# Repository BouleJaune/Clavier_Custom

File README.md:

# Clavier_Custom

Création d'un clavier avec un layout custom à partir de zéro.

Keyboard-layout.png et Raw_Layout_Data.txt représente le layout qui sera utilisé, généré via KLE.

CAD Case contient les fichiers .DXF pour découper les plaques d'aluminium qui serviront de "boitier".

CAD PCB contient le PCB exporté en .DXF pour comparer le placement des pas de vis avec le PCB.

PCB_vs_plaque.blender est le fichier blender permettant de voir qu'il n'y aura pas de soucis vis à vis des vis entrant en contact avec le PCB.

Scripting_Kicad contient les coordonnées des diodes et switchs sur le PCB ainsi qu'un petit script .py pour les placer automatiquement dans Kicad.

Kicad contient les librairies utilisées ainsi que le projet Kicad (PCB et& schématique).

Encore une hésitation sur l'utilisation d'une simple Teensy++ 2.0 ou alors la création complète du micro-contrôleur ce qui implique de burn un bootloader et gérer les soudures complexes.

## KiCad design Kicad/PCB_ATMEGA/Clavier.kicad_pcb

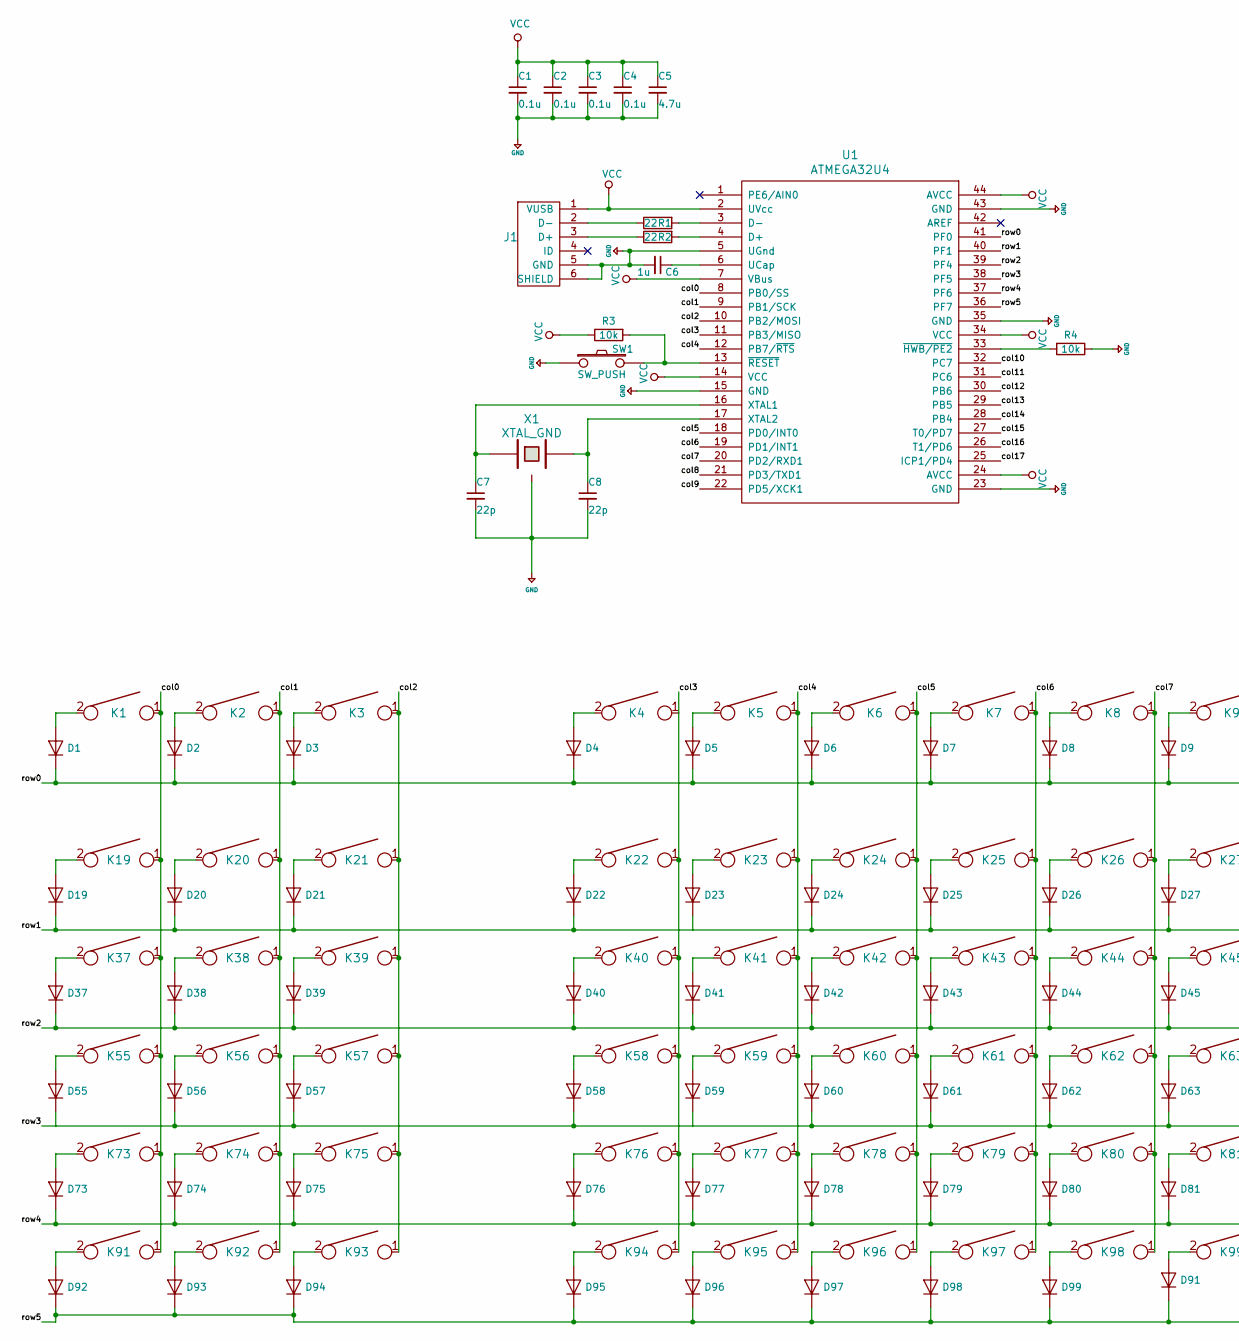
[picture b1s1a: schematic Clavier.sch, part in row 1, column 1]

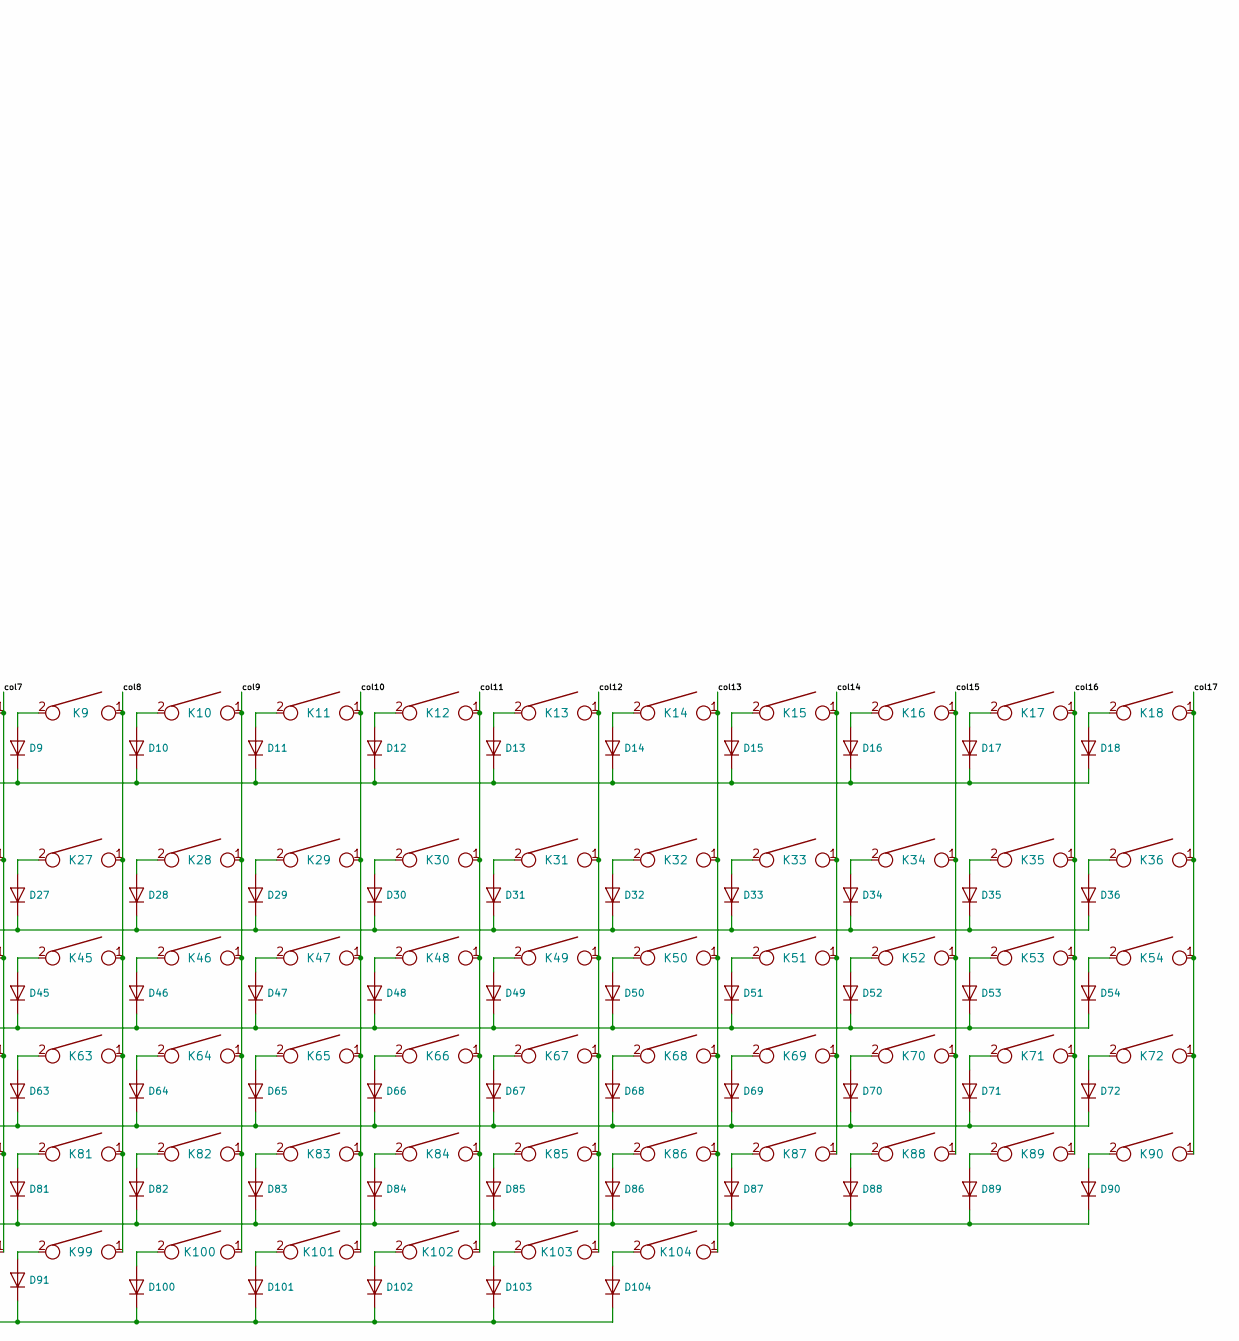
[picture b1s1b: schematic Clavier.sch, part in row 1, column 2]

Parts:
C1, C2, C3, C4: 0.1u; C_0805_2012Metric_Pad1.15x1.40mm_HandSolder
C5: 4.7u; C_0805_2012Metric_Pad1.15x1.40mm_HandSolder
C6: 1u; C_0805_2012Metric_Pad1.15x1.40mm_HandSolder
C7, C8: 22p; C_0805_2012Metric_Pad1.15x1.40mm_HandSolder
D1, D2, D3, D4, D5, D6, D7, D8, D9, D10, D11, D12, D13, D14, D15, D16, D17, D18, D19, D20, D21, D22, D23, D24, D25, D26, D27, D28, D29, D30, D31, D32, D33, D34, D35, D36, D37, D38, D39, D40, D41, D42, D43, D44, D45, D46, D47, D48, D49, D50, D51, D52, D53, D54, D55, D56, D57, D58, D59, D60, D61, D62, D63, D64, D65, D66, D67, D68, D69, D70, D71, D72, D73, D74, D75, D76, D77, D78, D79, D80, D81, D82, D83, D84, D85, D86, D87, D88, D89, D90, D91, D92, D93, D94, D95, D96, D97, D98, D99, D100, D101, D102, D103, D104: D; D_SOD123_axial
J1: USB_mini_micro_B; USB_miniB_hirose_5S8
K1, K2, K3, K4, K5, K6, K7, K8, K9, K10, K11, K12, K13, K14, K15, K16, K17, K18, K19, K20, K21, K22, K23, K24, K25, K26, K27, K28, K29, K30, K31, K32, K33, K34, K35, K36, K37, K38, K39, K40, K41, K42, K43, K44, K45, K46, K47, K48, K49, K50, K51, K52, K53, K54, K55, K56, K57, K58, K59, K60, K61, K62, K63, K64, K65, K66, K67, K68, K69, K70, K71, K72, K73, K74, K75, K76, K77, K78, K79, K80, K81, K82, K83, K84, K85, K86, K87, K88, K89, K90, K91, K92, K93, K94, K95, K96, K97, K98, K99, K100, K101, K102, K103, K104: KEYSW; Mx_Alps_100
R1, R2: 22; R_0805_2012Metric_Pad1.15x1.40mm_HandSolder
R3, R4: 10k; R_0805_2012Metric_Pad1.15x1.40mm_HandSolder
SW1: SW_PUSH; SW_SPST_TL3342
U1: ATMEGA32U4; TQFP-44_10x10mm_P0.8mm
X1: XTAL_GND; FA-238

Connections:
+5V: C1.2, C2.2, C3.2, C4.2, C5.2, C6.2, C7.2, C8.2, J1.5 (GND), J1.6 (SHIELD), R4.1, SW1.1, U1.5 (UGnd), U1.15 (GND), U1.23 (GND), U1.35 (GND), U1.43 (GND), X1.3
/col0: K1.1, K19.1, K37.1, K55.1, K73.1, K91.1, U1.8 (PB0/SS)
/col1: K2.1, K20.1, K38.1, K56.1, K74.1, K92.1, U1.9 (PB1/SCK)
/col2: K3.1, K21.1, K39.1, K57.1, K75.1, K93.1, U1.10 (PB2/MOSI)
/col3: K4.1, K22.1, K40.1, K58.1, K76.1, K94.1, U1.11 (PB3/MISO)
/col4: K5.1, K23.1, K41.1, K59.1, K77.1, K95.1, U1.12 (PB7/~RTS)
/col5: K6.1, K24.1, K42.1, K60.1, K78.1, K96.1, U1.18 (PD0/INT0)
/col6: K7.1, K25.1, K43.1, K61.1, K79.1, K97.1, U1.19 (PD1/INT1)
/col7: K8.1, K26.1, K44.1, K62.1, K80.1, K98.1, U1.20 (PD2/RXD1)
/col8: K9.1, K27.1, K45.1, K63.1, K81.1, K99.1, U1.21 (PD3/TXD1)
/col9: K10.1, K28.1, K46.1, K64.1, K82.1, K100.1, U1.22 (PD5/XCK1)
/col10: K11.1, K29.1, K47.1, K65.1, K83.1, K101.1, U1.32 (PC7)
/col11: K12.1, K30.1, K48.1, K66.1, K84.1, K102.1, U1.31 (PC6)
/col12: K13.1, K31.1, K49.1, K67.1, K85.1, K103.1, U1.30 (PB6)
/col13: K14.1, K32.1, K50.1, K68.1, K86.1, K104.1, U1.29 (PB5)
/col14: K15.1, K33.1, K51.1, K69.1, K87.1, U1.28 (PB4)
/col15: K16.1, K34.1, K52.1, K70.1, K88.1, U1.27 (T0/PD7)
/col16: K17.1, K35.1, K53.1, K71.1, K89.1, U1.26 (T1/PD6)
/col17: K18.1, K36.1, K54.1, K72.1, K90.1, U1.25 (ICP1/PD4)
/row0: D1.1 (K), D2.1 (K), D3.1 (K), D4.1 (K), D5.1 (K), D6.1 (K), D7.1 (K), D8.1 (K), D9.1 (K), D10.1 (K), D11.1 (K), D12.1 (K), D13.1 (K), D14.1 (K), D15.1 (K), D16.1 (K), D17.1 (K), D18.1 (K), U1.41 (PF0)
/row1: D19.1 (K), D20.1 (K), D21.1 (K), D22.1 (K), D23.1 (K), D24.1 (K), D25.1 (K), D26.1 (K), D27.1 (K), D28.1 (K), D29.1 (K), D30.1 (K), D31.1 (K), D32.1 (K), D33.1 (K), D34.1 (K), D35.1 (K), D36.1 (K), U1.40 (PF1)
/row2: D37.1 (K), D38.1 (K), D39.1 (K), D40.1 (K), D41.1 (K), D42.1 (K), D43.1 (K), D44.1 (K), D45.1 (K), D46.1 (K), D47.1 (K), D48.1 (K), D49.1 (K), D50.1 (K), D51.1 (K), D52.1 (K), D53.1 (K), D54.1 (K), U1.39 (PF4)
/row3: D55.1 (K), D56.1 (K), D57.1 (K), D58.1 (K), D59.1 (K), D60.1 (K), D61.1 (K), D62.1 (K), D63.1 (K), D64.1 (K), D65.1 (K), D66.1 (K), D67.1 (K), D68.1 (K), D69.1 (K), D70.1 (K), D71.1 (K), D72.1 (K), U1.38 (PF5)
/row4: D73.1 (K), D74.1 (K), D75.1 (K), D76.1 (K), D77.1 (K), D78.1 (K), D79.1 (K), D80.1 (K), D81.1 (K), D82.1 (K), D83.1 (K), D84.1 (K), D85.1 (K), D86.1 (K), D87.1 (K), D88.1 (K), D89.1 (K), D90.1 (K), U1.37 (PF6)
/row5: D91.1 (K), D92.1 (K), D93.1 (K), D94.1 (K), D95.1 (K), D96.1 (K), D97.1 (K), D98.1 (K), D99.1 (K), D100.1 (K), D101.1 (K), D102.1 (K), D103.1 (K), D104.1 (K), U1.36 (PF7)
unnamed: C6.1, U1.6 (UCap)
unnamed: C7.1, U1.16 (XTAL1), X1.1
unnamed: C8.1, U1.17 (XTAL2), X1.2
unnamed: D1.2 (A), K1.2
unnamed: D2.2 (A), K2.2
unnamed: D3.2 (A), K3.2
unnamed: D4.2 (A), K4.2
unnamed: D5.2 (A), K5.2
unnamed: D6.2 (A), K6.2
unnamed: D7.2 (A), K7.2
unnamed: D8.2 (A), K8.2
unnamed: D9.2 (A), K9.2
unnamed: D10.2 (A), K10.2
unnamed: D11.2 (A), K11.2
unnamed: D12.2 (A), K12.2
unnamed: D13.2 (A), K13.2
unnamed: D14.2 (A), K14.2
unnamed: D15.2 (A), K15.2
unnamed: D16.2 (A), K16.2
unnamed: D17.2 (A), K17.2
unnamed: D18.2 (A), K18.2
unnamed: D19.2 (A), K19.2
unnamed: D20.2 (A), K20.2
unnamed: D21.2 (A), K21.2
unnamed: D22.2 (A), K22.2
unnamed: D23.2 (A), K23.2
unnamed: D24.2 (A), K24.2
unnamed: D25.2 (A), K25.2
unnamed: D26.2 (A), K26.2
unnamed: D27.2 (A), K27.2
unnamed: D28.2 (A), K28.2
unnamed: D29.2 (A), K29.2
unnamed: D30.2 (A), K30.2
unnamed: D31.2 (A), K31.2
unnamed: D32.2 (A), K32.2
unnamed: D33.2 (A), K33.2
unnamed: D34.2 (A), K34.2
unnamed: D35.2 (A), K35.2
unnamed: D36.2 (A), K36.2
unnamed: D37.2 (A), K37.2
unnamed: D38.2 (A), K38.2
unnamed: D39.2 (A), K39.2
unnamed: D40.2 (A), K40.2
unnamed: D41.2 (A), K41.2
unnamed: D42.2 (A), K42.2
unnamed: D43.2 (A), K43.2
unnamed: D44.2 (A), K44.2
unnamed: D45.2 (A), K45.2
unnamed: D46.2 (A), K46.2
unnamed: D47.2 (A), K47.2
unnamed: D48.2 (A), K48.2
unnamed: D49.2 (A), K49.2
unnamed: D50.2 (A), K50.2
unnamed: D51.2 (A), K51.2
unnamed: D52.2 (A), K52.2
unnamed: D53.2 (A), K53.2
unnamed: D54.2 (A), K54.2
unnamed: D55.2 (A), K55.2
unnamed: D56.2 (A), K56.2
unnamed: D57.2 (A), K57.2
unnamed: D58.2 (A), K58.2
unnamed: D59.2 (A), K59.2
unnamed: D60.2 (A), K60.2
unnamed: D61.2 (A), K61.2
unnamed: D62.2 (A), K62.2
unnamed: D63.2 (A), K63.2
unnamed: D64.2 (A), K64.2
unnamed: D65.2 (A), K65.2
unnamed: D66.2 (A), K66.2
unnamed: D67.2 (A), K67.2
unnamed: D68.2 (A), K68.2
unnamed: D69.2 (A), K69.2
unnamed: D70.2 (A), K70.2
unnamed: D71.2 (A), K71.2
unnamed: D72.2 (A), K72.2
unnamed: D73.2 (A), K73.2
unnamed: D74.2 (A), K74.2
unnamed: D75.2 (A), K75.2
unnamed: D76.2 (A), K76.2
unnamed: D77.2 (A), K77.2
unnamed: D78.2 (A), K78.2
unnamed: D79.2 (A), K79.2
unnamed: D80.2 (A), K80.2
unnamed: D81.2 (A), K81.2
unnamed: D82.2 (A), K82.2
unnamed: D83.2 (A), K83.2
unnamed: D84.2 (A), K84.2
unnamed: D85.2 (A), K85.2
unnamed: D86.2 (A), K86.2
unnamed: D87.2 (A), K87.2
unnamed: D88.2 (A), K88.2
unnamed: D89.2 (A), K89.2
unnamed: D90.2 (A), K90.2
unnamed: D91.2 (A), K99.2
unnamed: D92.2 (A), K91.2
unnamed: D93.2 (A), K92.2
unnamed: D94.2 (A), K93.2
unnamed: D95.2 (A), K94.2
unnamed: D96.2 (A), K95.2
unnamed: D97.2 (A), K96.2
unnamed: D98.2 (A), K97.2
unnamed: D99.2 (A), K98.2
unnamed: D100.2 (A), K100.2
unnamed: D101.2 (A), K101.2
unnamed: D102.2 (A), K102.2
unnamed: D103.2 (A), K103.2
unnamed: D104.2 (A), K104.2
unnamed: J1.2 (D-), R1.1
unnamed: J1.3 (D+), R2.1
unnamed: R1.2, U1.3 (D-)
unnamed: R2.2, U1.4 (D+)
unnamed: R3.2, SW1.2, U1.13 (~RESET)
unnamed: R4.2, U1.33 (~HWB/PE2)
VCC: C1.1, C2.1, C3.1, C4.1, C5.1, J1.1 (VUSB), R3.1, U1.2 (UVcc), U1.7 (VBus), U1.14 (VCC), U1.24 (AVCC), U1.34 (VCC), U1.44 (AVCC)

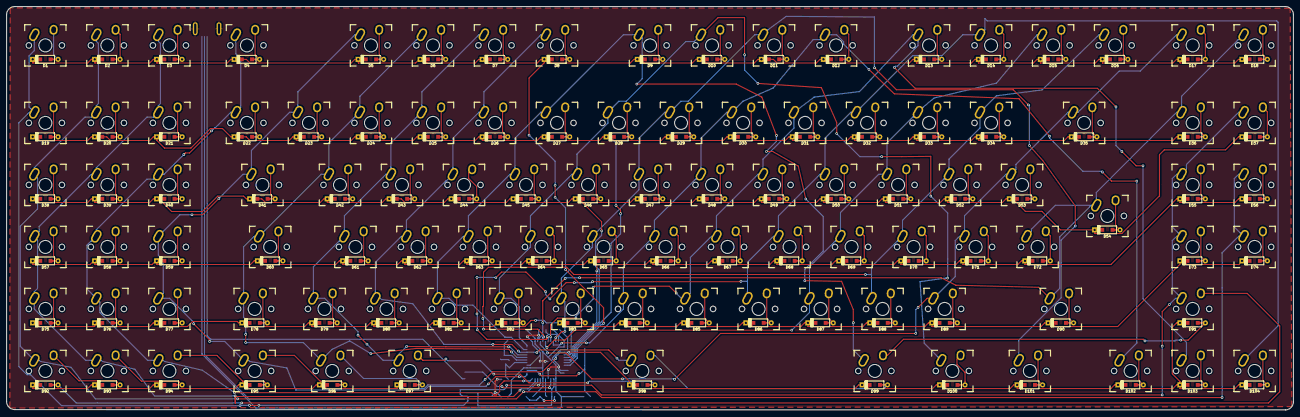
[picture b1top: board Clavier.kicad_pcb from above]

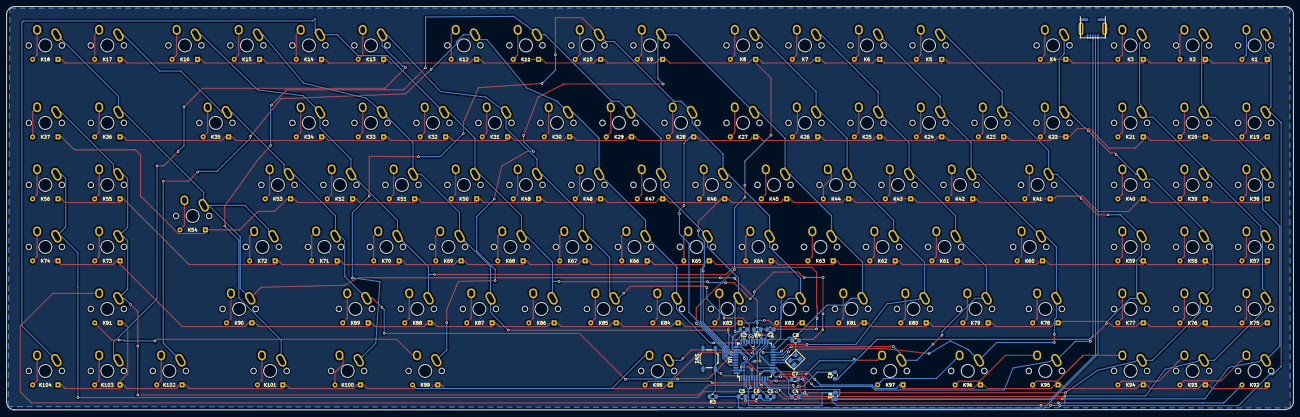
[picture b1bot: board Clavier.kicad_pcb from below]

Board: 2 copper layers, 395.3 x 123.9 mm, 224 parts (16 on the bottom side), 139 nets.
